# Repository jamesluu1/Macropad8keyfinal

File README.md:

# Macropad8keyfinal
Macropad8key Stardance Challenge
This is an 8 key macropad intended to assist you in functions like copy paste or whatever you prefer. 
It utilises 8 cherry mx keys, a fully 3d printed case running on Seeedstudio Xiao RP2040

CAD 

Made using fusion 360 software
It utilises 4 M3 screws to lock in place the Case top with the base (2 part case)

PCB

Schematic

Pcb 

Firmware 
If I'm being completely honest, I never intended to learn how to code or build firmware so i utilised ai to help me with the KMK firmware as I wasnt able to find any QMK firmware for my specific design

PARTS TO MAKE THIS
- 8 cherry Mx switches
- 8 DSA keycaps
- 4 M3x16mm SHCS Bolts
- 8 1N4148 DO-35 Diodes.
- 1 XIAO RP2040
- 1 Case (2 printed parts, the top and the base)

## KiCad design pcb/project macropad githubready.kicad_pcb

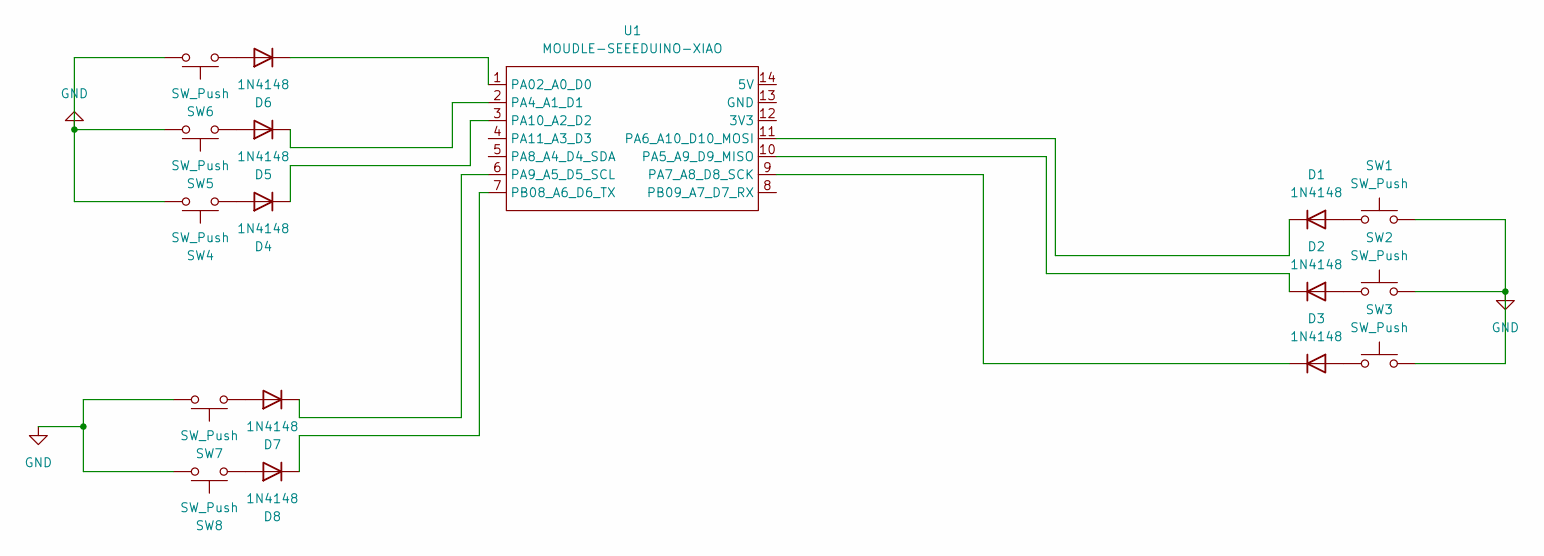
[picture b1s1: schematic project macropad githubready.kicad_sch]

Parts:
D1, D2, D3, D4, D5, D6, D7, D8: 1N4148; D_DO-35_SOD27_P7.62mm_Horizontal
SW1, SW2, SW3, SW4, SW5, SW6, SW7, SW8: SW_Push; SW_Cherry_MX_1.00u_PCB
U1: MOUDLE-SEEEDUINO-XIAO; MCU_Seeed_ESP32C3

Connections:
GND: SW1.2, SW2.2, SW3.2, SW4.2, SW5.2, SW6.2, SW7.2, SW8.2
unnamed: D1.2 (A), SW1.1
unnamed: D1.1 (K), U1.11 (PA6_A10_D10_MOSI)
unnamed: D2.2 (A), SW2.1
unnamed: D2.1 (K), U1.10 (PA5_A9_D9_MISO)
unnamed: D3.2 (A), SW3.1
unnamed: D3.1 (K), U1.9 (PA7_A8_D8_SCK)
unnamed: D4.2 (A), SW4.1
unnamed: D4.1 (K), U1.3 (PA10_A2_D2)
unnamed: D5.2 (A), SW5.1
unnamed: D5.1 (K), U1.2 (PA4_A1_D1)
unnamed: D6.2 (A), SW6.1
unnamed: D6.1 (K), U1.1 (PA02_A0_D0)
unnamed: D7.2 (A), SW7.1
unnamed: D7.1 (K), U1.6 (PA9_A5_D5_SCL)
unnamed: D8.2 (A), SW8.1
unnamed: D8.1 (K), U1.7 (PB08_A6_D6_TX)

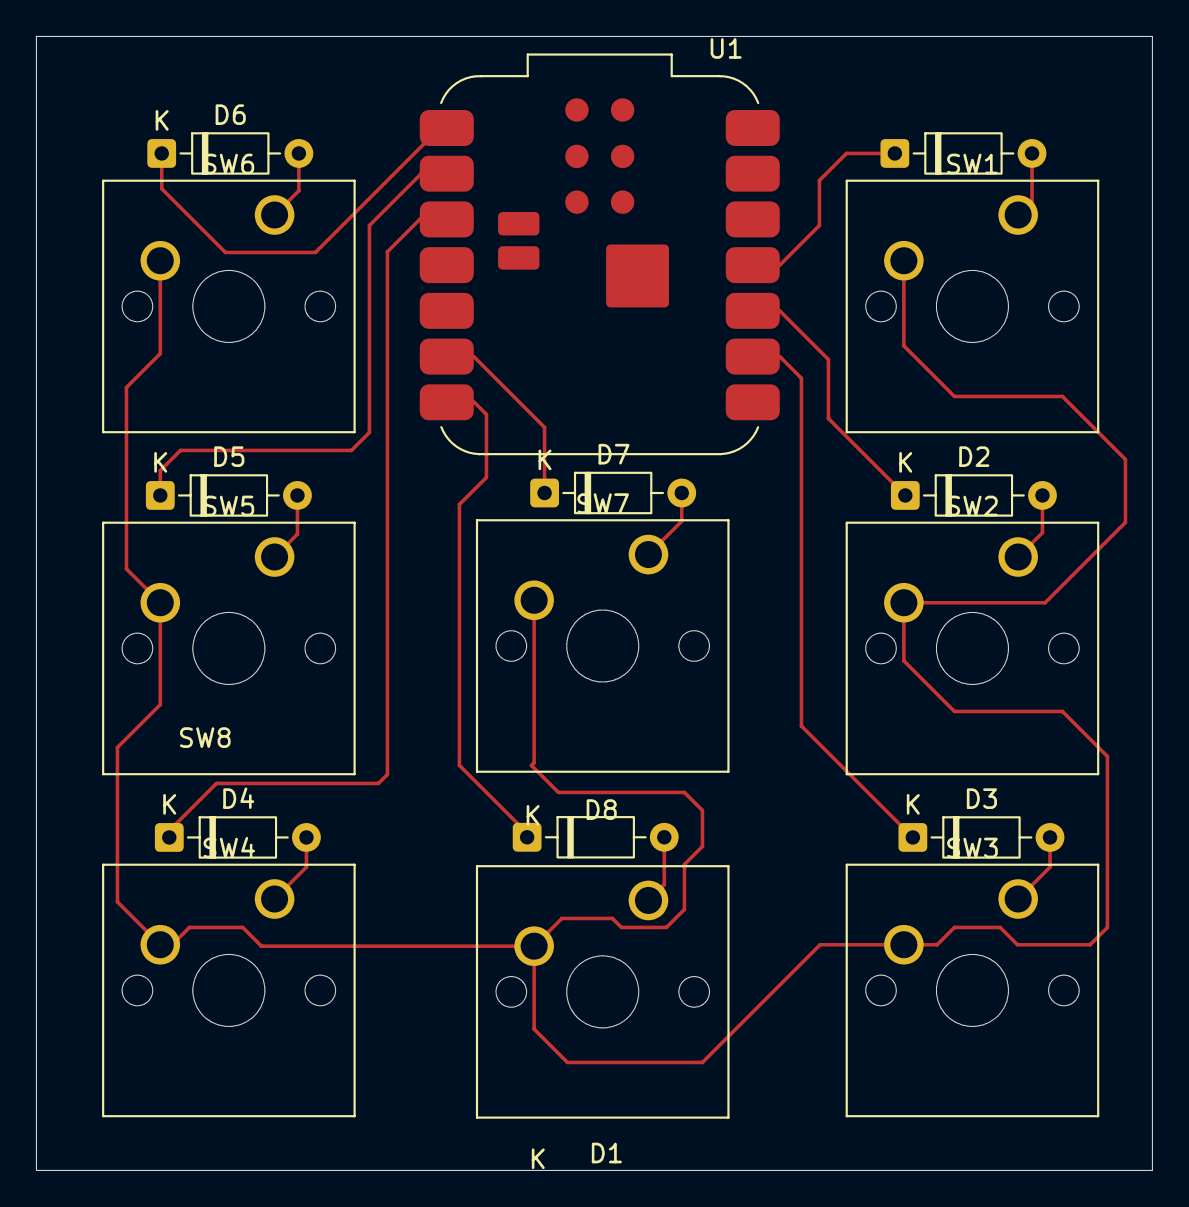
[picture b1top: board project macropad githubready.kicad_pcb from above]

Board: 2 copper layers, 62.0 x 63.0 mm, 17 parts (0 on the bottom side), 17 nets.
